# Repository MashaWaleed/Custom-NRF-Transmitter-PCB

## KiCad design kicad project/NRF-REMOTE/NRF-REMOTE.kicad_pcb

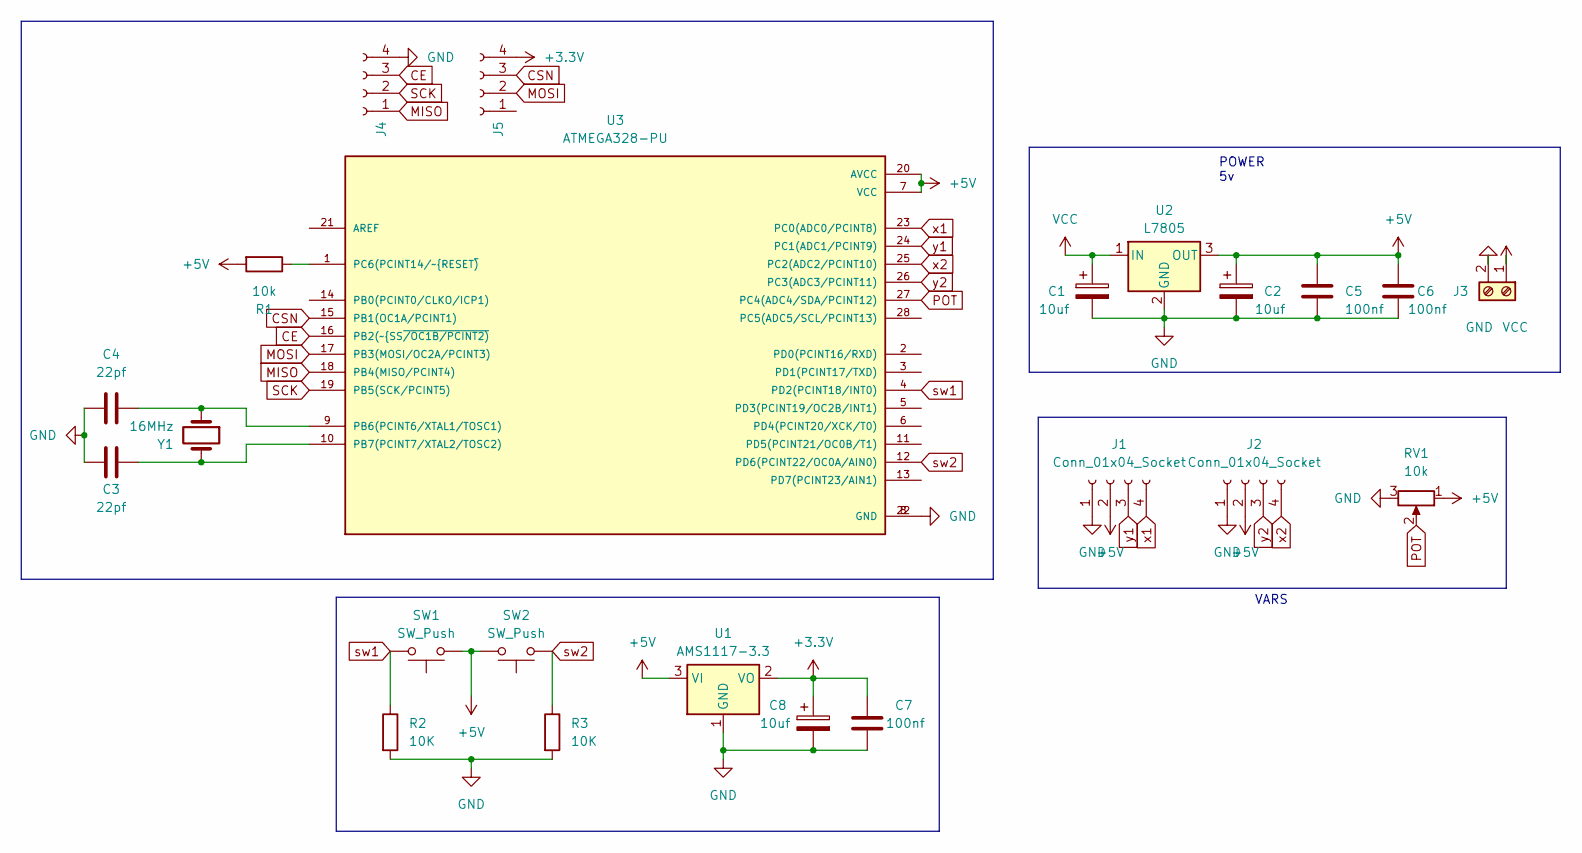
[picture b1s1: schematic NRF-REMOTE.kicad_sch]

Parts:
C1, C2, C8: 10uf; C_Disc_D3.4mm_W2.1mm_P2.50mm
C3, C4: 22pf; C_Disc_D3.4mm_W2.1mm_P2.50mm
C5, C6, C7: 100nf; C_Disc_D3.4mm_W2.1mm_P2.50mm
J1, J2, J4, J5: Conn_01x04_Socket; PinSocket_1x04_P2.54mm_Vertical
J3: Screw_Terminal_01x02; TerminalBlock_bornier-2_P5.08mm
R1: 10k; R_Axial_DIN0207_L6.3mm_D2.5mm_P10.16mm_Horizontal
R2, R3: 10K; R_Axial_DIN0207_L6.3mm_D2.5mm_P10.16mm_Horizontal
RV1: 10k; Potentiometer_Omeg_PC16BU_Vertical
SW1, SW2: SW_Push; SW_PUSH-12mm
U1: AMS1117-3.3; SOT-223-3_TabPin2
U2: L7805; Converter_DCDC_TRACO_TSR-1_THT
U3: ATMEGA328-PU; DIP787W46P254L3467H508Q28; PARTREV B
Y1: 16MHz; Resonator-2Pin_W6.0mm_H3.0mm

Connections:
+3.3V: C7.1, C8.1, J5.4, U1.2 (VO)
+5V: C2.1, C5.1, C6.1, J1.2, J2.2, R1.2, RV1.1, SW1.1, SW2.2, U1.3 (VI), U2.3 (OUT), U3.7 (VCC), U3.20 (AVCC)
CE: J4.3, U3.16 (PB2(~SS~{/OC1B/PCINT2))
CSN: J5.3, U3.15 (PB1(OC1A/PCINT1))
GND: C1.2, C2.2, C3.1, C4.2, C5.2, C6.2, C7.2, C8.2, J1.1, J2.1, J3.2, J4.4, R2.2, R3.2, RV1.3, U1.1 (GND), U2.2 (GND), U3.8 (GND), U3.22 (GND)
MISO: J4.1, U3.18 (PB4(MISO/PCINT4))
MOSI: J5.2, U3.17 (PB3(MOSI/OC2A/PCINT3))
unnamed: C4.1, U3.9 (PB6(PCINT6/XTAL1/TOSC1)), Y1.1
unnamed: C3.2, U3.10 (PB7(PCINT7/XTAL2/TOSC2)), Y1.2
unnamed: R1.1, U3.1 (PC6(PCINT14/~RESET~{))
POT: RV1.2, U3.27 (PC4(ADC4/SDA/PCINT12))
SCK: J4.2, U3.19 (PB5(SCK/PCINT5))
VCC: C1.1, J3.1, U2.1 (IN)
sw1: R2.1, SW1.2, U3.4 (PD2(PCINT18/INT0))
sw2: R3.1, SW2.1, U3.12 (PD6(PCINT22/OC0A/AIN0))
x1: J1.4, U3.23 (PC0(ADC0/PCINT8))
x2: J2.4, U3.25 (PC2(ADC2/PCINT10))
y1: J1.3, U3.24 (PC1(ADC1/PCINT9))
y2: J2.3, U3.26 (PC3(ADC3/PCINT11))

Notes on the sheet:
VARS
POWER 5v

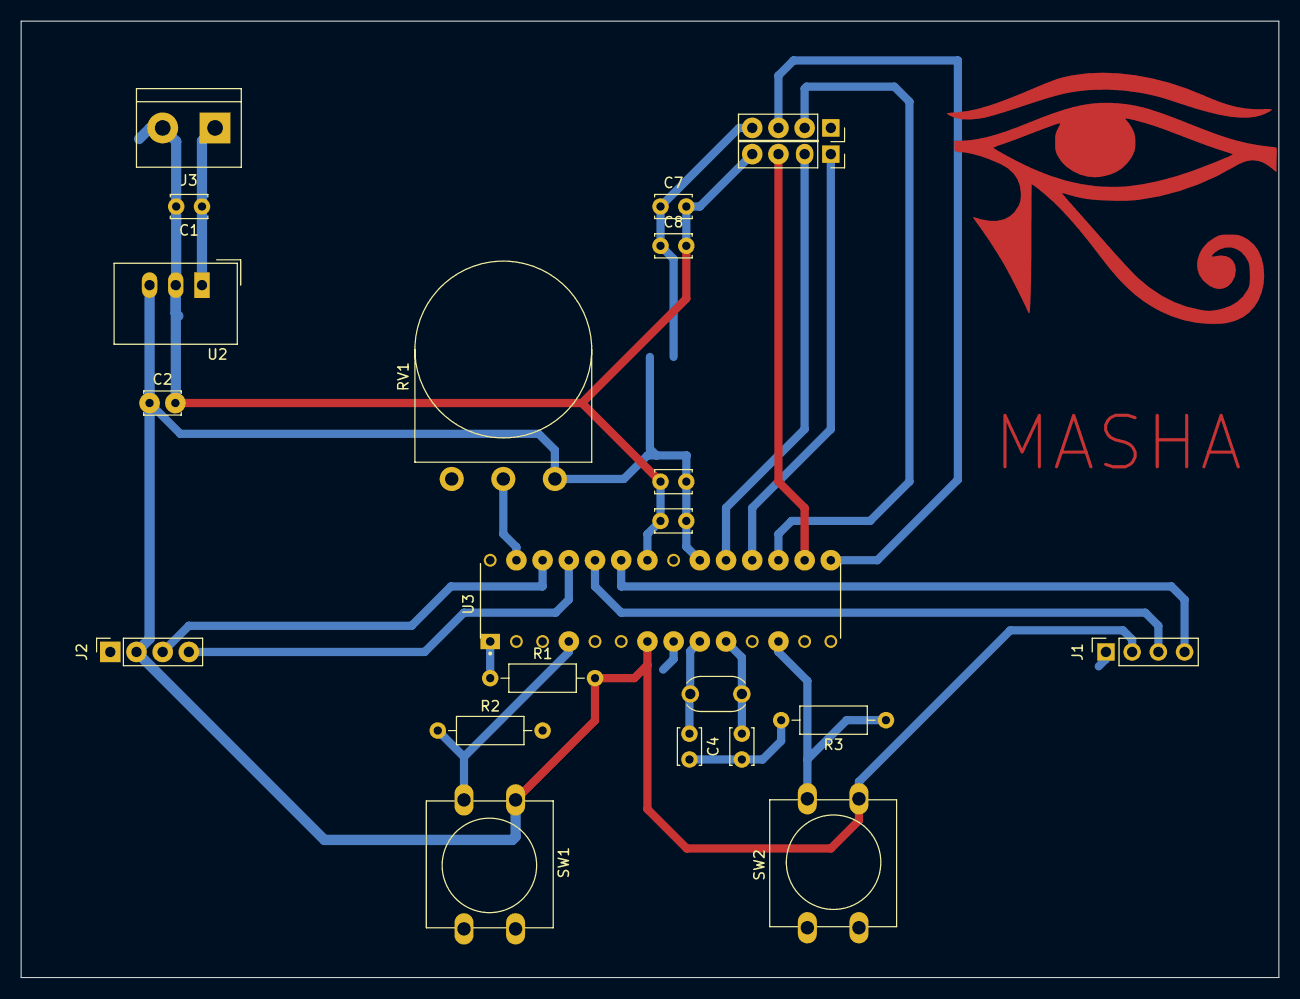
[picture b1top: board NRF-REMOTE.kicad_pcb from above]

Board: 2 copper layers, 121.9 x 92.7 mm, 23 parts (1 on the bottom side), 19 nets.

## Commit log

2023-08-09 finished
